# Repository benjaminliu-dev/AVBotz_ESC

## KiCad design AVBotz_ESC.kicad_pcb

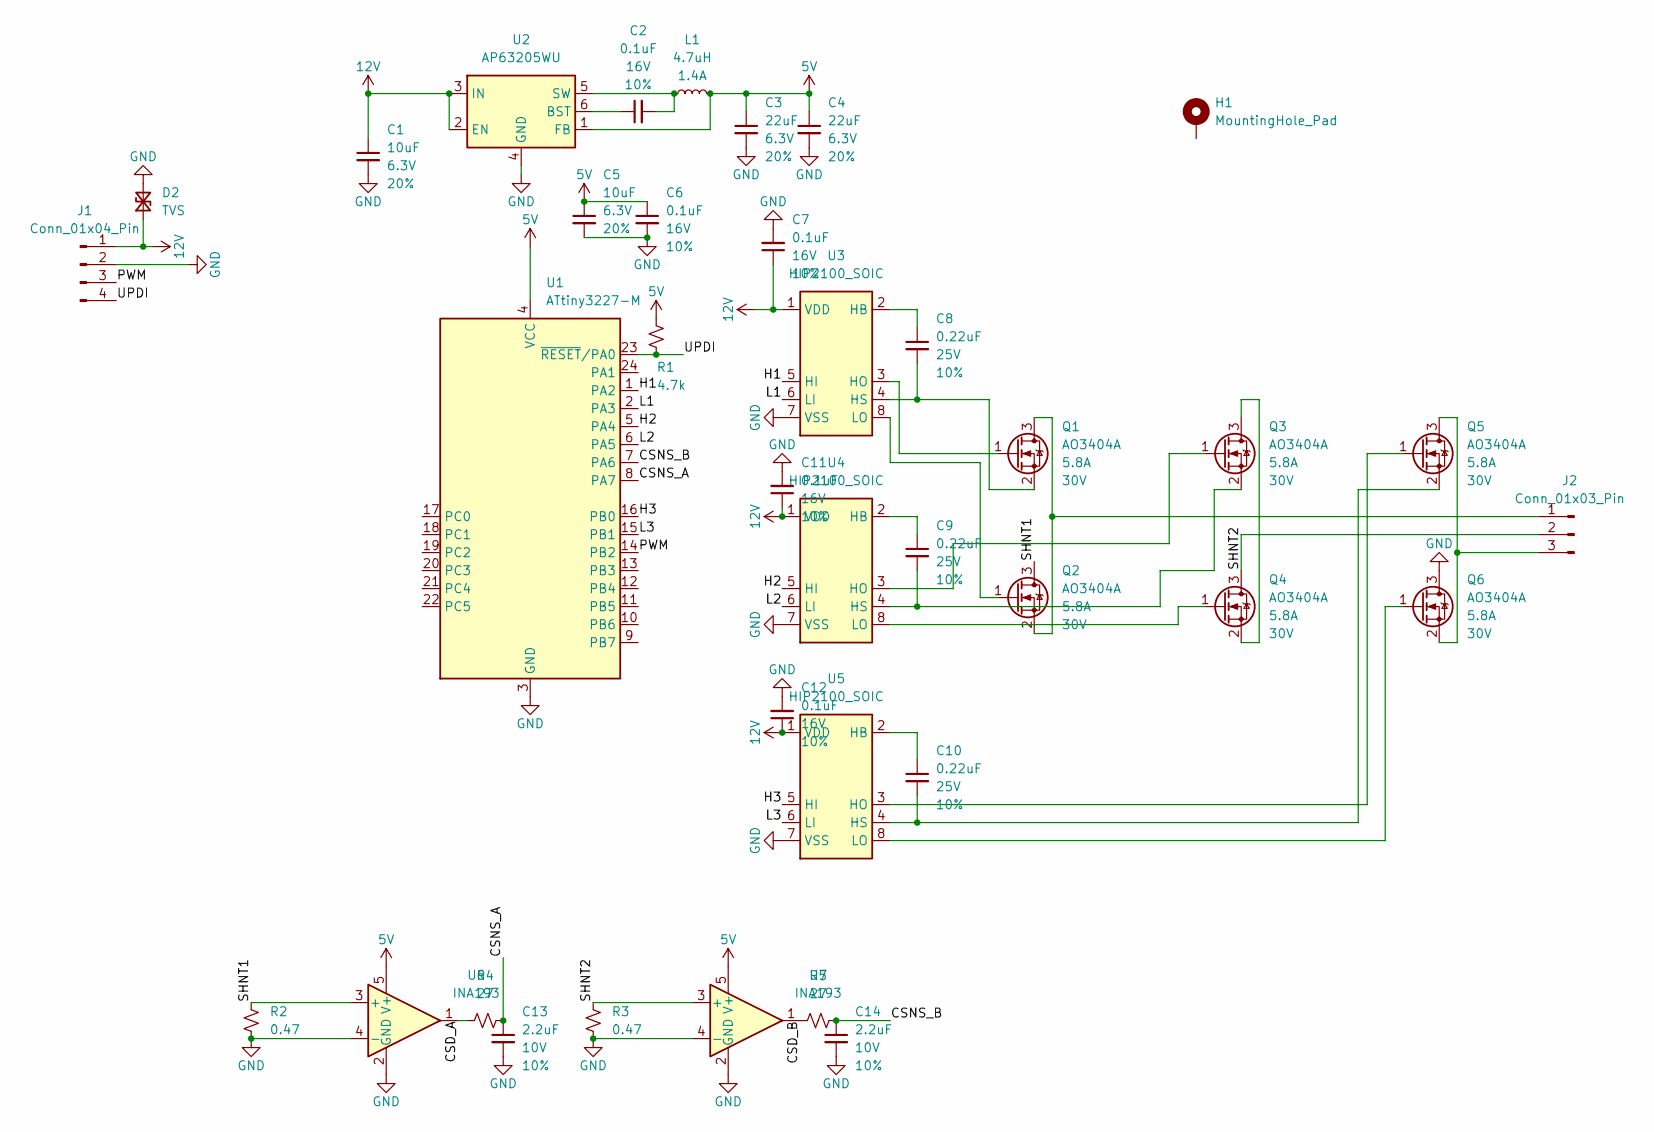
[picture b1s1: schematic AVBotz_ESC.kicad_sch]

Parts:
C1, C5: 10uF; C_0402_1005Metric; Voltage 6.3V; Tolerance 20%
C2, C6, C7, C11, C12: 0.1uF; C_0402_1005Metric; Voltage 16V; Tolerance 10%
C3, C4: 22uF; C_0603_1608Metric; Voltage 6.3V; Tolerance 20%
C8, C9, C10: 0.22uF; C_0603_1608Metric; Voltage 25V; Tolerance 10%
C13, C14: 2.2uF; C_0402_1005Metric; Voltage 10V; Tolerance 10%
D2: TVS; SOT-363
H1: MountingHole_Pad; MountingHole_2.2mm_M2_DIN965_Pad
J1: Conn_01x04_Pin; JST_1x04_P1.0mm_Horizontal_SMD
J2: Conn_01x03_Pin; JST_1x03_P1.0mm_Horizontal_SMD
L1: 4.7uH; 1008_2520Metric
Q1, Q2, Q3, Q4, Q5, Q6: AO3404A; SOT23-3
R1: 4.7k; R_0402_1005Metric
R2, R3: 0.47; R_0603_1608Metric
R4, R5: 27; R_0402_1005Metric
U1: ATtiny3227-M; QFN-24-1EP_4x4mm_P0.5mm_EP2.6x2.6mm
U2: AP63205WU; TSOT-23-6
U3, U4, U5: HIP2100_SOIC; SOIC-8_3.9x4.9mm_P1.27mm
U6, U7: INA193; SOT-23-5

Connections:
5V: C3.1, C4.1, C5.1, C6.1, L1.2, R1.2, U1.4 (VCC), U2.1 (FB), U6.5 (V+), U7.5 (V+)
12V: C1.1, C7.1, C11.1, C12.1, D2.1 (A1), J1.1, U2.2 (EN), U2.3 (IN), U3.1 (VDD), U4.1 (VDD), U5.1 (VDD)
/CSD_A: R4.1, U6.1
/CSD_B: R5.1, U7.1
/CSNS_A: C13.1, R4.2, U1.8 (PA7)
/CSNS_B: C14.1, R5.2, U1.7 (PA6)
/H1: U1.1 (PA2), U3.5 (HI)
/H2: U1.5 (PA4), U4.5 (HI)
/H3: U1.16 (PB0), U5.5 (HI)
/L1: U1.2 (PA3), U3.6 (LI)
/L2: U1.6 (PA5), U4.6 (LI)
/L3: U1.15 (PB1), U5.6 (LI)
/PWM: J1.3, U1.14 (PB2)
/SHNT1: Q2.3 (D), R2.2, U6.3 (+)
/SHNT2: J2.2, Q4.3 (D), R3.2, U7.3 (+)
/UPDI: J1.4, R1.1, U1.23 (~RESET/PA0)
GND: C1.2, C3.2, C4.2, C5.2, C6.2, C7.2, C11.2, C12.2, C13.2, C14.2, D2.2 (A2), J1.2, Q6.3 (D), R2.1, R3.1, U1.3 (GND), U1.25 (GND), U2.4 (GND), U3.7 (VSS), U4.7 (VSS), U5.7 (VSS), U6.2 (GND), U6.4 (-), U7.2 (GND), U7.4 (-)
unnamed: J2.1, Q1.3 (D), Q2.2 (S)
unnamed: J2.3, Q5.3 (D), Q6.2 (S)
unnamed: Q1.1 (G), U3.3 (HO)
unnamed: C8.2, Q1.2 (S), U3.4 (HS)
unnamed: Q2.1 (G), U3.8 (LO)
unnamed: Q3.3 (D), Q4.2 (S)
unnamed: Q3.1 (G), U4.3 (HO)
unnamed: C9.2, Q3.2 (S), U4.4 (HS)
unnamed: Q4.1 (G), U4.8 (LO)
unnamed: Q5.1 (G), U5.3 (HO)
unnamed: C10.2, Q5.2 (S), U5.4 (HS)
unnamed: Q6.1 (G), U5.8 (LO)
unnamed: C2.1, U2.6 (BST)
unnamed: C2.2, L1.1, U2.5 (SW)
unnamed: C8.1, U3.2 (HB)
unnamed: C9.1, U4.2 (HB)
unnamed: C10.1, U5.2 (HB)

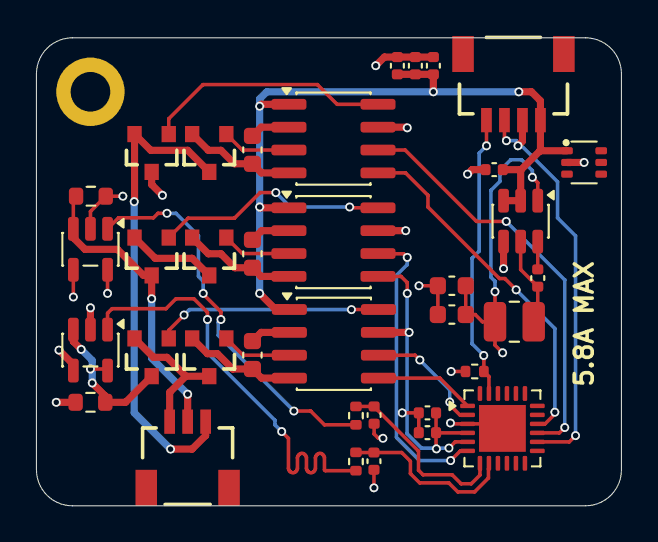
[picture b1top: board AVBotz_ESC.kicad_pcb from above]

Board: 4 copper layers, 32.5 x 26.0 mm, 37 parts (0 on the bottom side), 34 nets.

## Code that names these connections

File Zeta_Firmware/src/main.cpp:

#include <Arduino.h>
#include "utils.h"

#define H1 PIN_PB0
#define H2 PIN_PB1
#define H3 PIN_PB2
#define L1 PIN_PA3
#define L2 PIN_PA4
#define L3 PIN_PA5

#define CSNS_A PIN_PA7
#define CSNS_B PIN_PA6
#define THROTTLE_PIN PIN_PA1
#define PWM THROTTLE_PIN

#define PWM_PERIOD 1000U
#define PWM_MIN 40U
#define ADC_SAMPLES 4U

static const uint8_t PHASE_TABLE[6][2] = {
    {0, 1},
    {0, 2},
    {1, 2},
    {1, 0},
    {2, 0},
    {2, 1}};

static uint8_t g_comm_step = 0;

static void set_high_side_pwm(uint8_t phase, uint16_t duty)
{
    uint16_t safeDuty = duty > PWM_PERIOD ? PWM_PERIOD : duty;

    switch (phase)
    {
    case 0:
        TCA0.SINGLE.CMP0 = safeDuty;
        break;
    case 1:
        TCA0.SINGLE.CMP1 = safeDuty;
        break;
    case 2:
        TCA0.SINGLE.CMP2 = safeDuty;
        break;
    default:
        break;
    }
}

static void set_low_side(uint8_t phase, bool active)
{
    uint8_t pin = 0;

    switch (phase)
    {
    case 0:
        pin = L1;
        break;
    case 1:
        pin = L2;
        break;
    case 2:
        pin = L3;
        break;
    default:
        return;
    }

    digitalWrite(pin, active ? LOW : HIGH);
}

static void all_phases_off(void)
{
    TCA0.SINGLE.CMP0 = 0;
    TCA0.SINGLE.CMP1 = 0;
    TCA0.SINGLE.CMP2 = 0;

    digitalWrite(L1, HIGH);
    digitalWrite(L2, HIGH);
    digitalWrite(L3, HIGH);
}

static void apply_commutation(uint16_t duty)
{
    const uint8_t high = PHASE_TABLE[g_comm_step][0];
    const uint8_t low = PHASE_TABLE[g_comm_step][1];

    all_phases_off();
    set_high_side_pwm(high, duty);
    set_low_side(low, true);
}

static void timer_init(void)
{
    TCA0.SINGLE.CTRLA = TCA_SINGLE_CLKSEL_DIV1_gc | TCA_SINGLE_ENABLE_bm;
    TCA0.SINGLE.CTRLB = TCA_SINGLE_CMP0EN_bm | TCA_SINGLE_CMP1EN_bm | TCA_SINGLE_CMP2EN_bm;
    TCA0.SINGLE.CTRLC = 0;
    TCA0.SINGLE.CTRLD = 0;
    TCA0.SINGLE.PER = PWM_PERIOD;
    TCA0.SINGLE.CNT = 0;
    TCA0.SINGLE.CMP0 = 0;
    TCA0.SINGLE.CMP1 = 0;
    TCA0.SINGLE.CMP2 = 0;
}

static void adc_init(void)
{
    ADC0.CTRLC = (uint8_t)ADC_PRESC_DIV16_gc | (uint8_t)ADC_REFSEL_VDD_gc;
    ADC0.CTRLB = (uint8_t)ADC_MODE_SINGLE_12BIT_gc;
    ADC0.CTRLA = ADC_ENABLE_bm;
    ADC0.INTCTRL = 0;
    ADC0.INTFLAGS = ADC_RESRDY_bm;
    ADC0.MUXPOS = ADC_MUXPOS_AIN7_gc;
    ADC0.MUXNEG = ADC_MUXNEG_GND_gc;
}

static uint16_t adc_read_channel(uint8_t muxPos)
{
    uint32_t sum = 0;

    for (uint8_t i = 0; i < ADC_SAMPLES; ++i)
    {
        ADC0.MUXPOS = muxPos;
        ADC0.COMMAND = ADC_START_IMMEDIATE_gc;
        while (!(ADC0.INTFLAGS & ADC_RESRDY_bm))
        {
            ;
        }
        ADC0.INTFLAGS = ADC_RESRDY_bm;
        sum += (uint16_t)ADC0.RESULT;
    }

    return (uint16_t)(sum / ADC_SAMPLES);
}

static uint16_t read_throttle_pwm_percent(void)
{
    const float duty = getDutyCycle(PWM);
    if (duty < 0.0f)
    {
        return 0;
    }
    if (duty > 100.0f)
    {
        return 100;
    }
    return (uint16_t)duty;
}

void setup()
{
    pinMode(H1, OUTPUT);
    pinMode(H2, OUTPUT);
    pinMode(H3, OUTPUT);
    pinMode(L1, OUTPUT);
    pinMode(L2, OUTPUT);
    pinMode(L3, OUTPUT);
    pinMode(PWM, INPUT);

    digitalWrite(H1, LOW);
    digitalWrite(H2, LOW);
    digitalWrite(H3, LOW);
    digitalWrite(L1, HIGH);
    digitalWrite(L2, HIGH);
    digitalWrite(L3, HIGH);

    timer_init();
    adc_init();
    all_phases_off();

    analogReadResolution(12);
    analogReference(VDD);
}

void loop()
{
    static uint32_t lastStepMs = 0;
    static uint16_t lastDuty = 0;

    uint16_t throttlePct = read_throttle_pwm_percent();
    uint16_t duty = (uint16_t)((uint32_t)throttlePct * PWM_PERIOD / 100U);

    const uint16_t currentSense = adc_read_channel(ADC_MUXPOS_AIN7_gc);
    const uint16_t bemfSense = adc_read_channel(ADC_MUXPOS_AIN6_gc);

    if (millis() - lastStepMs > 4)
    {
        if (throttlePct > 5U)
        {
            g_comm_step = (g_comm_step + 1U) % 6U;
        }
        else
        {
            g_comm_step = 0U;
            all_phases_off();
        }
        lastStepMs = millis();
    }

    if (throttlePct <= 5U)
    {
        all_phases_off();
        lastDuty = 0;
        return;
    }

    if (duty > PWM_MIN && duty != lastDuty)
    {
        apply_commutation(duty);
        lastDuty = duty;
    }

    if (currentSense > 3800U || bemfSense > 3900U)
    {
        all_phases_off();
        g_comm_step = 0U;
    }
}
